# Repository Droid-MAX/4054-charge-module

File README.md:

# 4054-charge-module
4054 Power and Charging module

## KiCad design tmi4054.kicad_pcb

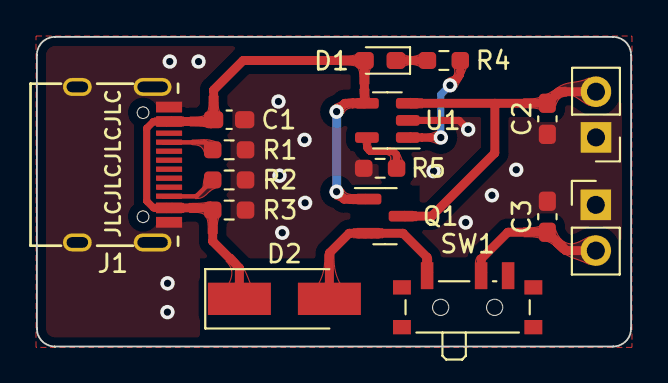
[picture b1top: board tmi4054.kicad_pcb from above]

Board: 2 copper layers, 33.0 x 17.2 mm, 16 parts (0 on the bottom side), 10 nets.

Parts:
C1, C2: 10uF; C_0603_1608Metric_Pad1.08x0.95mm_HandSolder
C3: 22uF; C_0603_1608Metric_Pad1.08x0.95mm_HandSolder
D1: LED; LED_0603_1608Metric_Pad1.05x0.95mm_HandSolder
D2: SS22; D_SMA_Handsoldering
J1: USB_C_Receptacle_USB2.0; USB-C_16Pin
J2, J3: Conn_01x02_Male; PinHeader_1x02_P2.54mm_Vertical
Q1: AO3401A; SOT-23
R1, R2: 5.1K; R_0603_1608Metric_Pad0.98x0.95mm_HandSolder
R3: 10K; R_0603_1608Metric_Pad0.98x0.95mm_HandSolder
R4: 1K; R_0603_1608Metric_Pad0.98x0.95mm_HandSolder
R5: 1.4K; R_0603_1608Metric_Pad0.98x0.95mm_HandSolder
SW1: SW_SPDT; SW_SPDT_PCM12
U1: LTC4054ES5-4.2; TSOT-23-5

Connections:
/VBAT: C2.1, J2.2, Q1.3 (D), U1.3 (BAT)
/VOUT: C3.1, J3.2, SW1.2 (B)
GND: C1.1, C2.2, C3.2, J1.A1 (GND), J1.B1 (GND), J1.S1 (SHIELD), J2.1, J3.1, R1.2, R2.2, R3.2, R5.1, U1.2 (GND)
unnamed: D1.1 (K), R4.1
unnamed: D2.2 (A), Q1.2 (S), SW1.1 (A)
unnamed: J1.A5 (CC1), R1.1
unnamed: J1.B5 (CC2), R2.1
unnamed: R4.2, U1.1 (~CHRG)
unnamed: R5.2, U1.5 (PROG)
VCC: C1.2, D1.2 (A), D2.1 (K), J1.A4 (VBUS), J1.B4 (VBUS), Q1.1 (G), R3.1, U1.4 (VCC)

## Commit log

2022-12-08 Release version 1.0
2022-12-09 adjust pmos model to AO3401A
